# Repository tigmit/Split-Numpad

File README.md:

# DIY NUMPAD -
#####    by TIGMIT

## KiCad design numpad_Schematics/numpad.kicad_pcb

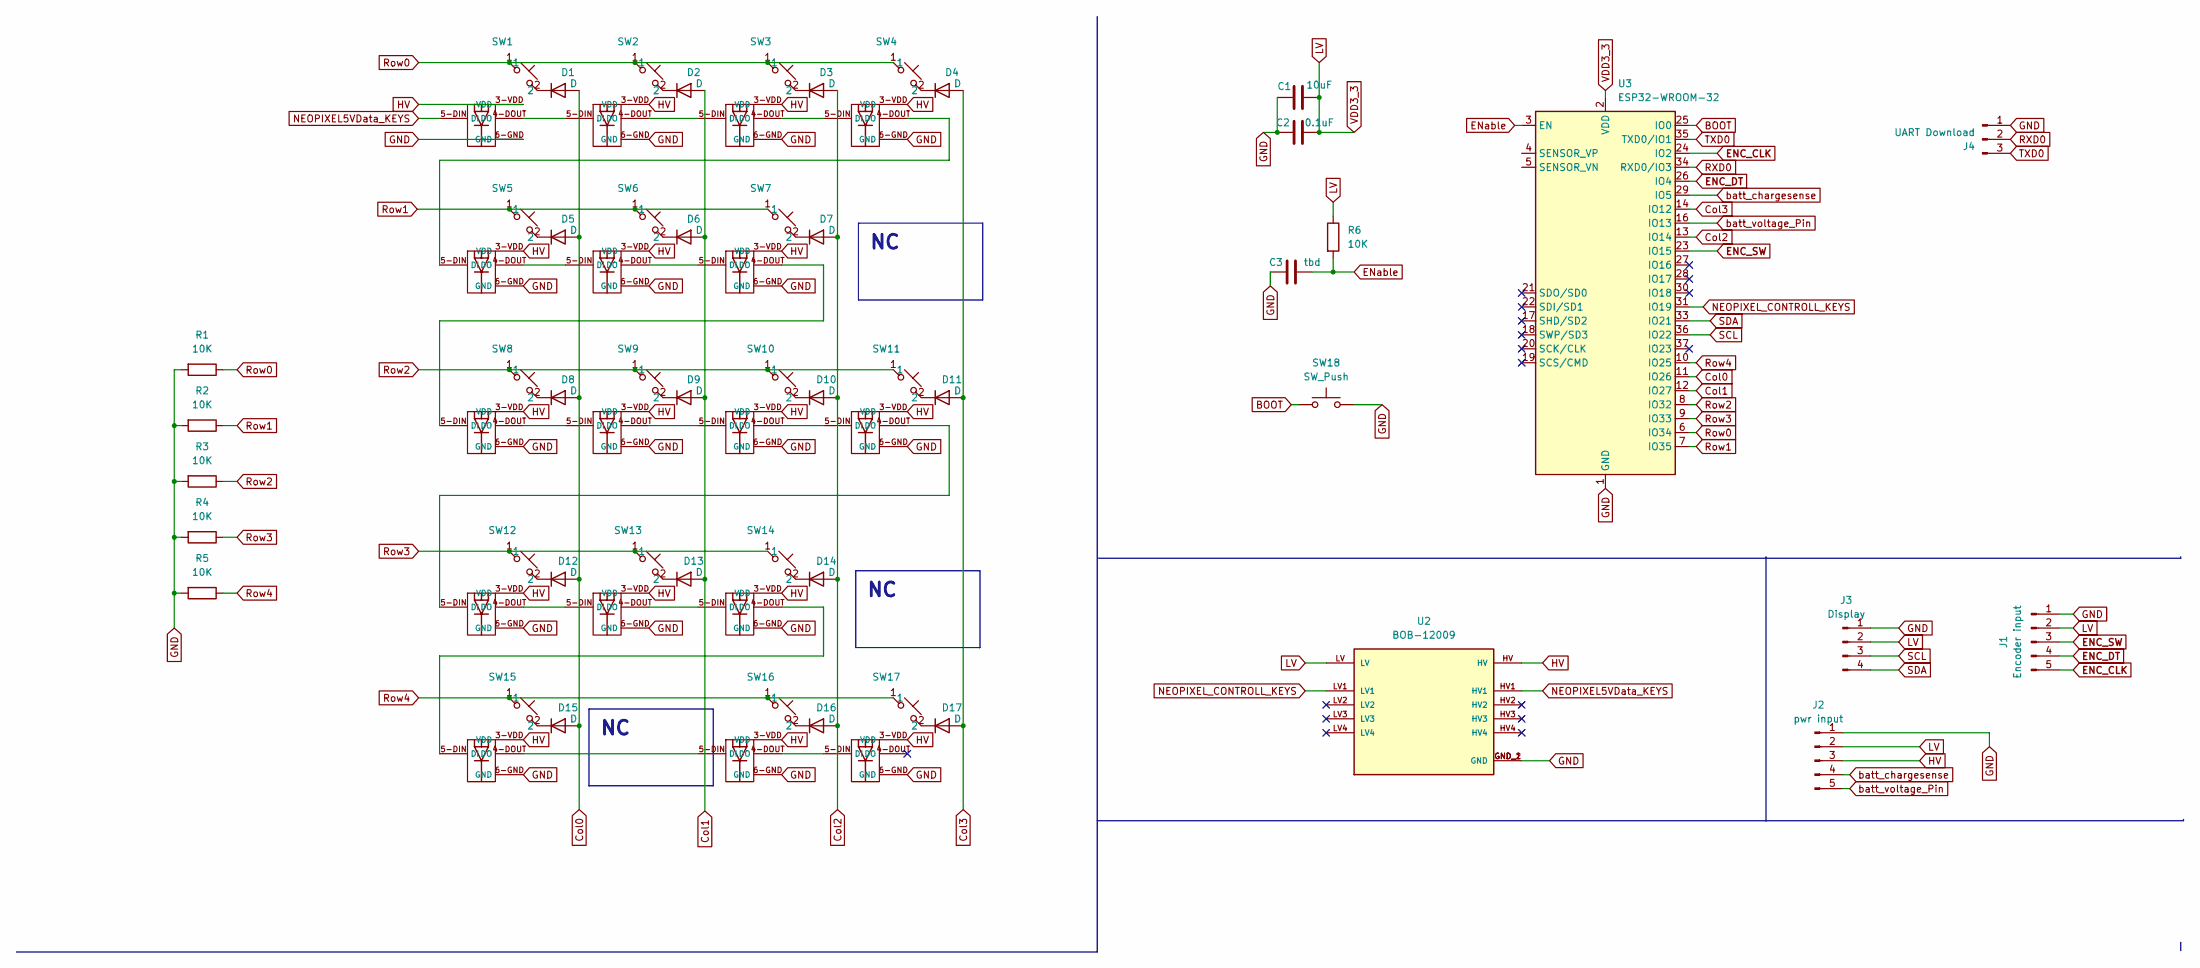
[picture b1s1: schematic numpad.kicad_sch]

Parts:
C1: 10uF; CP_EIA-3528-12_Kemet-T
C2: 0.1uF; CP_EIA-3528-12_Kemet-T
C3: tbd; CP_EIA-3528-12_Kemet-T
D1, D2, D3, D4, D5, D6, D7, D8, D9, D10, D11, D12, D13, D14, D15, D16, D17: D; Diode_SOD-123
J1: Encoder input; PinHeader_1x05_P2.54mm_Vertical
J2: pwr input; PinHeader_1x05_P2.54mm_Vertical
J3: Display; PinHeader_1x04_P2.54mm_Vertical
J4: UART Download; PinHeader_1x03_P2.54mm_Horizontal
R1, R2, R3, R4, R5, R6: 10K; R_Axial_DIN0204_L3.6mm_D1.6mm_P7.62mm_Horizontal
SW1, SW2, SW3, SW4, SW5, SW6, SW7, SW8, SW9, SW10, SW11, SW12, SW13, SW14, SW15, SW16, SW17: hotswap socket with neopixel
SW18: SW_Push; tigmit pushbutton
U2: BOB-12009; CONV_BOB-12009; PARTREV 01
U3: ESP32-WROOM-32; ESP32-WROOM-32 tigmit

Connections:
BOOT: SW18.1, U3.25 (IO0)
Col0: D1.2 (A), D5.2 (A), D8.2 (A), D12.2 (A), D15.2 (A), U3.11 (IO26)
Col1: D2.2 (A), D6.2 (A), D9.2 (A), D13.2 (A), U3.12 (IO27)
Col2: D3.2 (A), D7.2 (A), D10.2 (A), D14.2 (A), D16.2 (A), U3.13 (IO14)
Col3: D4.2 (A), D11.2 (A), D17.2 (A), U3.14 (IO12)
ENC_CLK: J1.5, U3.24 (IO2); also elsewhere on the board
ENC_DT: J1.4, U3.26 (IO4); also elsewhere on the board
ENC_SW: J1.3, U3.23 (IO15); also elsewhere on the board
ENable: C3.2, R6.2, U3.3 (EN)
GND: C1.1, C2.1, C3.1, J1.1, J2.1, J3.1, J4.1, R1.2, R2.2, R3.2, R4.2, R5.2, SW1.6-GND (GND), SW2.6-GND (GND), SW3.6-GND (GND), SW4.6-GND (GND), SW5.6-GND (GND), SW6.6-GND (GND), SW7.6-GND (GND), SW8.6-GND (GND), SW9.6-GND (GND), SW10.6-GND (GND), SW11.6-GND (GND), SW12.6-GND (GND), SW13.6-GND (GND), SW14.6-GND (GND), SW15.6-GND (GND), SW16.6-GND (GND), SW17.6-GND (GND), SW18.2, U2.GND_1 (GND), U2.GND_2 (GND), U3.1 (GND), U3.15 (GND), U3.38 (GND), U3.39 (GND); also elsewhere on the board
HV: J2.3, SW1.3-VDD (VDD), SW2.3-VDD (VDD), SW3.3-VDD (VDD), SW4.3-VDD (VDD), SW5.3-VDD (VDD), SW6.3-VDD (VDD), SW7.3-VDD (VDD), SW8.3-VDD (VDD), SW9.3-VDD (VDD), SW10.3-VDD (VDD), SW11.3-VDD (VDD), SW12.3-VDD (VDD), SW13.3-VDD (VDD), SW14.3-VDD (VDD), SW15.3-VDD (VDD), SW16.3-VDD (VDD), SW17.3-VDD (VDD), U2.HV; also elsewhere on the board
LV: C1.2, C2.2, J1.2, J2.2, J3.2, R6.1, U2.LV, U3.2 (VDD); also elsewhere on the board
NEOPIXEL5VData_KEYS: SW1.5-DIN (DI), U2.HV1; also elsewhere on the board
NEOPIXEL_CONTROLL_KEYS: U2.LV1, U3.31 (IO19); also elsewhere on the board
unnamed: D1.1 (K), SW1.2
unnamed: D2.1 (K), SW2.2
unnamed: D3.1 (K), SW3.2
unnamed: D4.1 (K), SW4.2
unnamed: D5.1 (K), SW5.2
unnamed: D6.1 (K), SW6.2
unnamed: D7.1 (K), SW7.2
unnamed: D8.1 (K), SW8.2
unnamed: D9.1 (K), SW9.2
unnamed: D10.1 (K), SW10.2
unnamed: D11.1 (K), SW11.2
unnamed: D12.1 (K), SW12.2
unnamed: D13.1 (K), SW13.2
unnamed: D14.1 (K), SW14.2
unnamed: D15.1 (K), SW15.2
unnamed: D16.1 (K), SW16.2
unnamed: D17.1 (K), SW17.2
unnamed: SW1.4-DOUT (DO), SW2.5-DIN (DI)
unnamed: SW2.4-DOUT (DO), SW3.5-DIN (DI)
unnamed: SW3.4-DOUT (DO), SW4.5-DIN (DI)
unnamed: SW4.4-DOUT (DO), SW5.5-DIN (DI)
unnamed: SW5.4-DOUT (DO), SW6.5-DIN (DI)
unnamed: SW6.4-DOUT (DO), SW7.5-DIN (DI)
unnamed: SW7.4-DOUT (DO), SW8.5-DIN (DI)
unnamed: SW8.4-DOUT (DO), SW9.5-DIN (DI)
unnamed: SW9.4-DOUT (DO), SW10.5-DIN (DI)
unnamed: SW10.4-DOUT (DO), SW11.5-DIN (DI)
unnamed: SW11.4-DOUT (DO), SW12.5-DIN (DI)
unnamed: SW12.4-DOUT (DO), SW13.5-DIN (DI)
unnamed: SW13.4-DOUT (DO), SW14.5-DIN (DI)
unnamed: SW14.4-DOUT (DO), SW15.5-DIN (DI)
unnamed: SW15.4-DOUT (DO), SW16.5-DIN (DI)
unnamed: SW16.4-DOUT (DO), SW17.5-DIN (DI)
RXD0: J4.2, U3.34 (RXD0/IO3); also elsewhere on the board
Row0: R1.1, SW1.1, SW2.1, SW3.1, SW4.1, U3.6 (IO34)
Row1: R2.1, SW5.1, SW6.1, SW7.1, U3.7 (IO35)
Row2: R3.1, SW8.1, SW9.1, SW10.1, SW11.1, U3.8 (IO32)
Row3: R4.1, SW12.1, SW13.1, SW14.1, U3.9 (IO33)
Row4: R5.1, SW15.1, SW16.1, SW17.1, U3.10 (IO25)
SCL: J3.3, U3.36 (IO22); also elsewhere on the board
SDA: J3.4, U3.33 (IO21); also elsewhere on the board
TXD0: J4.3, U3.35 (TXD0/IO1); also elsewhere on the board
batt_chargesense: J2.4, U3.29 (IO5); also elsewhere on the board
batt_voltage_Pin: J2.5, U3.16 (IO13); also elsewhere on the board

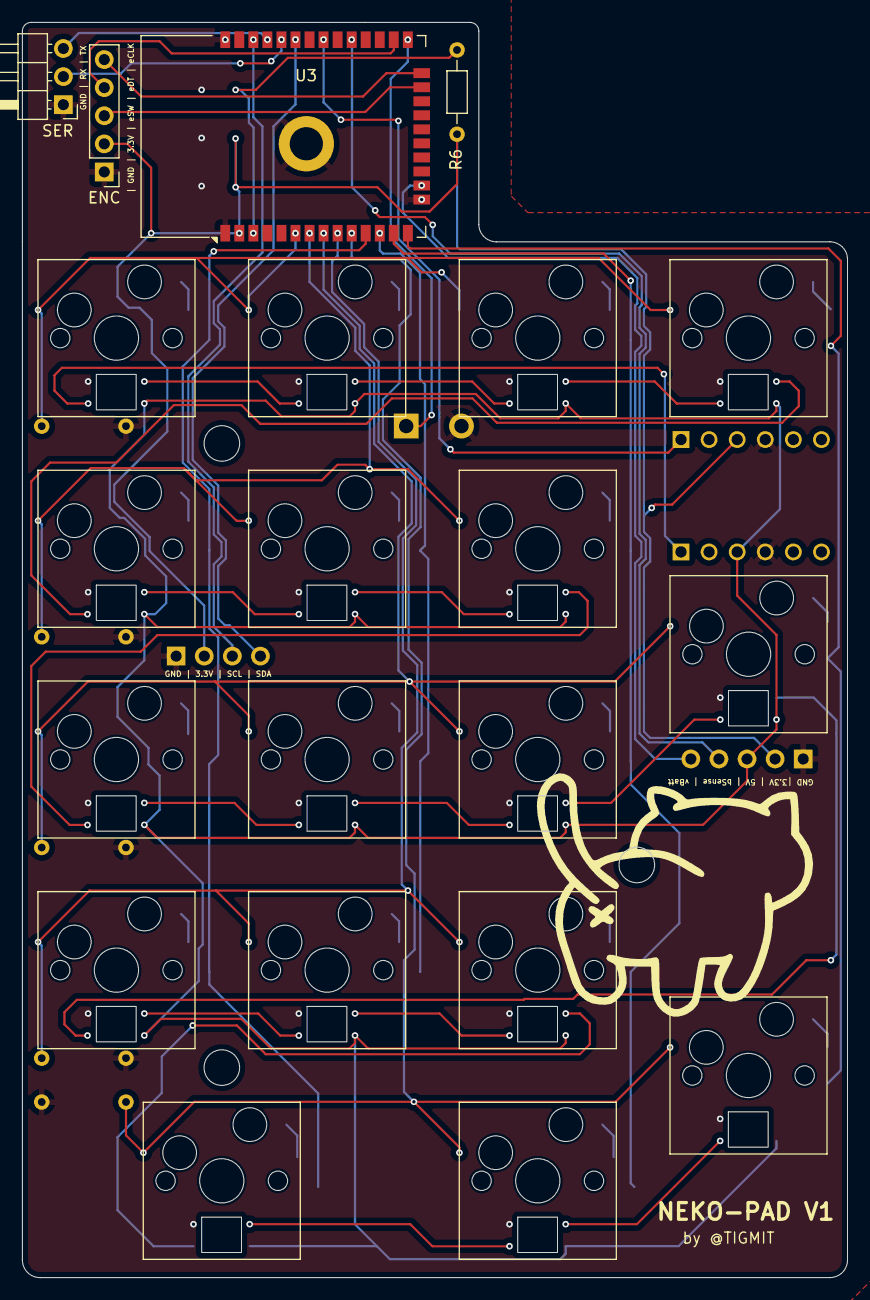
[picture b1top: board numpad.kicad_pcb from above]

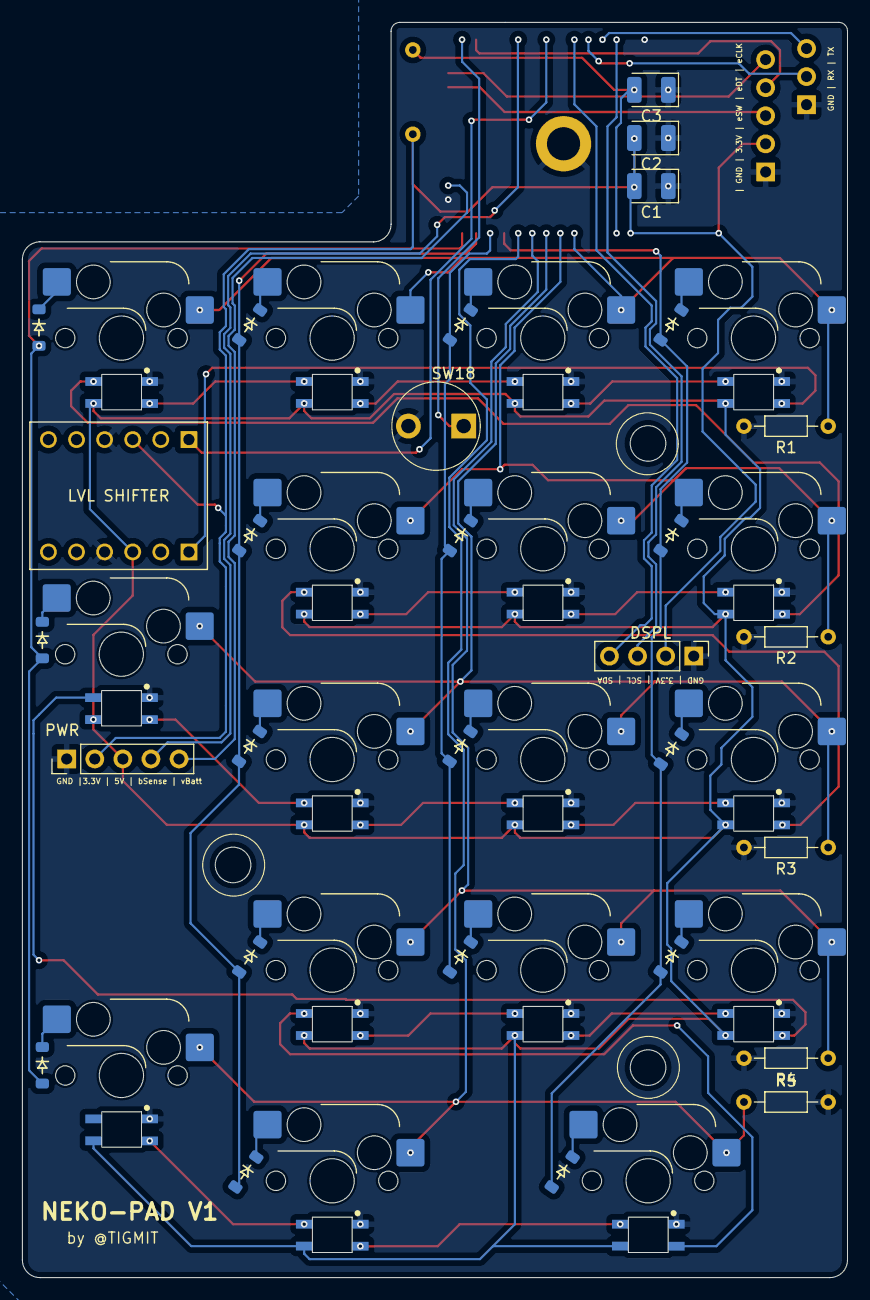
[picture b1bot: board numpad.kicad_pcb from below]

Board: 11 copper layers, 74.6 x 113.5 mm, 50 parts (29 on the bottom side), 58 nets.

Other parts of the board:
DSPL: Display; PinHeader_1x04_P2.54mm_Vertical
ENC: Encoder input; PinHeader_1x05_P2.54mm_Vertical
LVL SHIFTER: BOB-12009; CONV_BOB-12009
PWR: pwr input; PinHeader_1x05_P2.54mm_Vertical
SER: UART Download; PinHeader_1x03_P2.54mm_Horizontal

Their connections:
ENC_CLK: ENC.5; also elsewhere on the board
ENC_DT: ENC.4; also elsewhere on the board
ENC_SW: ENC.3; also elsewhere on the board
GND: DSPL.1, ENC.1, LVL SHIFTER.GND_1 (GND), LVL SHIFTER.GND_2 (GND), PWR.1, SER.1; also elsewhere on the board
HV: LVL SHIFTER.HV, PWR.3; also elsewhere on the board
LV: DSPL.2, ENC.2, LVL SHIFTER.LV, PWR.2; also elsewhere on the board
NEOPIXEL5VData_KEYS: LVL SHIFTER.HV1; also elsewhere on the board
NEOPIXEL_CONTROLL_KEYS: LVL SHIFTER.LV1; also elsewhere on the board
RXD0: SER.2; also elsewhere on the board
SCL: DSPL.3; also elsewhere on the board
SDA: DSPL.4; also elsewhere on the board
TXD0: SER.3; also elsewhere on the board
batt_chargesense: PWR.4; also elsewhere on the board
batt_voltage_Pin: PWR.5; also elsewhere on the board

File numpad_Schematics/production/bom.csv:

Designator,Footprint,Quantity,Value,LCSC Part #
C1,CP_EIA-3528-12_Kemet-T,1,10uF,
C2,CP_EIA-3528-12_Kemet-T,1,0.1uF,
C3,CP_EIA-3528-12_Kemet-T,1,tbd,
"D1, D10, D11, D12, D13, D14, D15, D16, D17, D2, D3, D4, D5, D6, D7, D8, D9",Diode_SOD-123,17,D,
DSPL,PinHeader_1x04_P2.54mm_Vertical,1,Display,
ENC,PinHeader_1x05_P2.54mm_Vertical,1,Encoder input,
LVL SHIFTER,CONV_BOB-12009,1,BOB-12009,
PWR,PinHeader_1x05_P2.54mm_Vertical,1,pwr input,
"R1, R2, R3, R4, R5, R6",R_Axial_DIN0204_L3.6mm_D1.6mm_P7.62mm_Horizontal,6,10K,
SER,PinHeader_1x03_P2.54mm_Horizontal,1,UART Download,
"SW1, SW10, SW11, SW12, SW13, SW14, SW15, SW16, SW17, SW2, SW3, SW4, SW5, SW6, SW7, SW8, SW9",hotswap socket with neopixel,17,~,
SW18,tigmit pushbutton,1,SW_Push,
U3,ESP32-WROOM-32 tigmit,1,ESP32-WROOM-32,

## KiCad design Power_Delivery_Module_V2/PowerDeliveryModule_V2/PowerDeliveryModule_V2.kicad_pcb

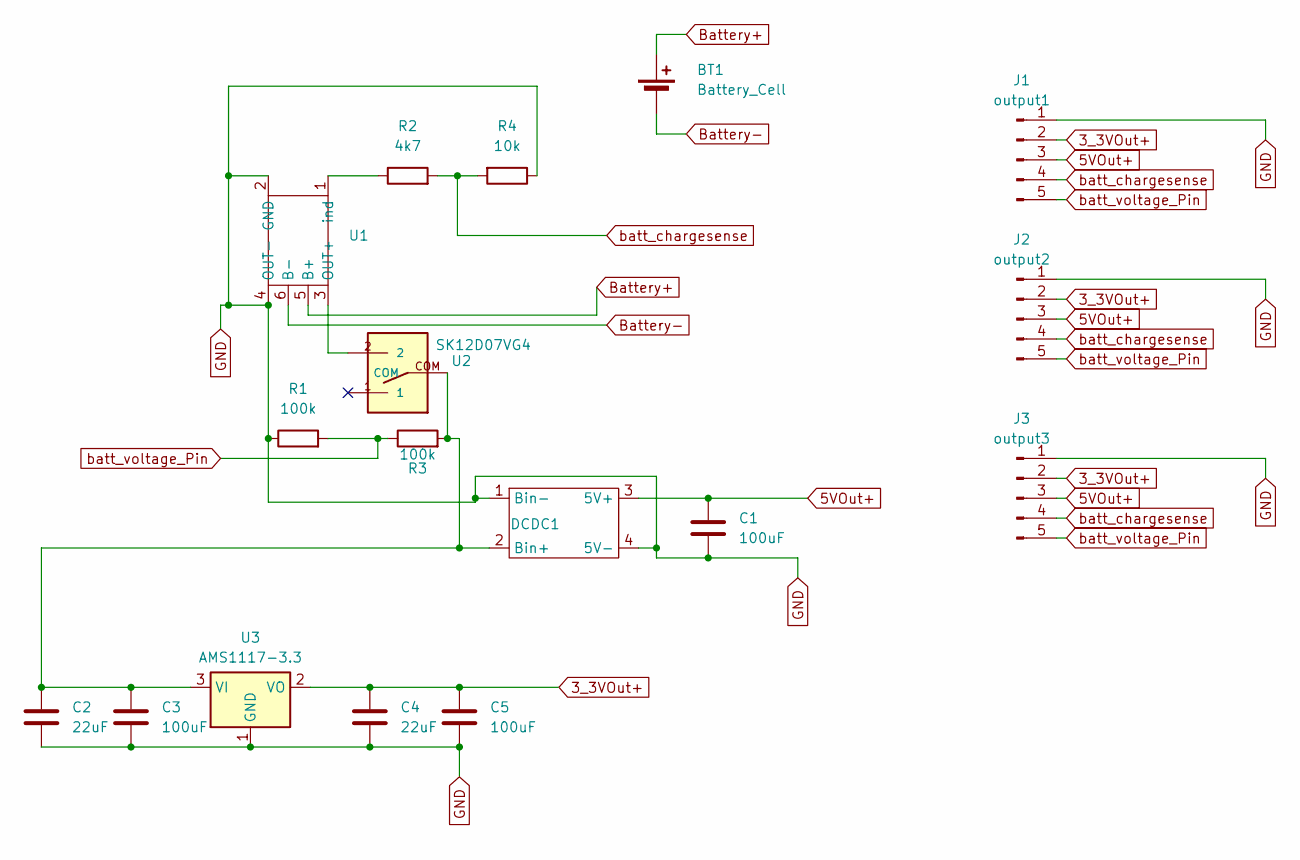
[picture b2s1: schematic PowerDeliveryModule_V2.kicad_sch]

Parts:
BT1: Battery_Cell; battery solder pins
C1, C3, C5: 100uF; CP_EIA-3528-12_Kemet-T
C2, C4: 22uF; CP_EIA-3528-12_Kemet-T
DCDC1: DCDC-Converter
J1: output1; PinHeader_1x05_P2.54mm_Vertical
J2: output2; PinHeader_1x05_P2.54mm_Vertical
J3: output3; PinHeader_1x05_P2.54mm_Vertical
R1, R3: 100k; R_Axial_DIN0204_L3.6mm_D1.6mm_P7.62mm_Horizontal
R2: 4k7; R_Axial_DIN0204_L3.6mm_D1.6mm_P7.62mm_Horizontal
R4: 10k; R_Axial_DIN0204_L3.6mm_D1.6mm_P7.62mm_Horizontal
U1: TP4056-18650
U2: SK12D07VG4
U3: AMS1117-3.3; SOT-223-3_TabPin2

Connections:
3_3VOut+: C4.1, C5.1, J1.2, J2.2, J3.2, U3.2 (VO)
5VOut+: C1.1, DCDC1.3 (5V+), J1.3, J2.3, J3.3
Battery+: BT1.1 (+), U1.5 (B+)
Battery-: BT1.2 (-), U1.6 (B-)
GND: C1.2, C2.2, C3.2, C4.2, C5.2, DCDC1.1 (Bin-), DCDC1.4 (5V-), J1.1, J2.1, J3.1, R1.1, R4.1, U1.2 (GND), U1.4 (OUT-), U3.1 (GND)
unnamed: C2.1, C3.1, DCDC1.2 (Bin+), R3.2, U2.COM, U3.3 (VI)
unnamed: U1.3 (OUT+), U2.2
unnamed: R2.1, U1.1 (ind)
batt_chargesense: J1.4, J2.4, J3.4, R2.2, R4.2
batt_voltage_Pin: J1.5, J2.5, J3.5, R1.2, R3.1

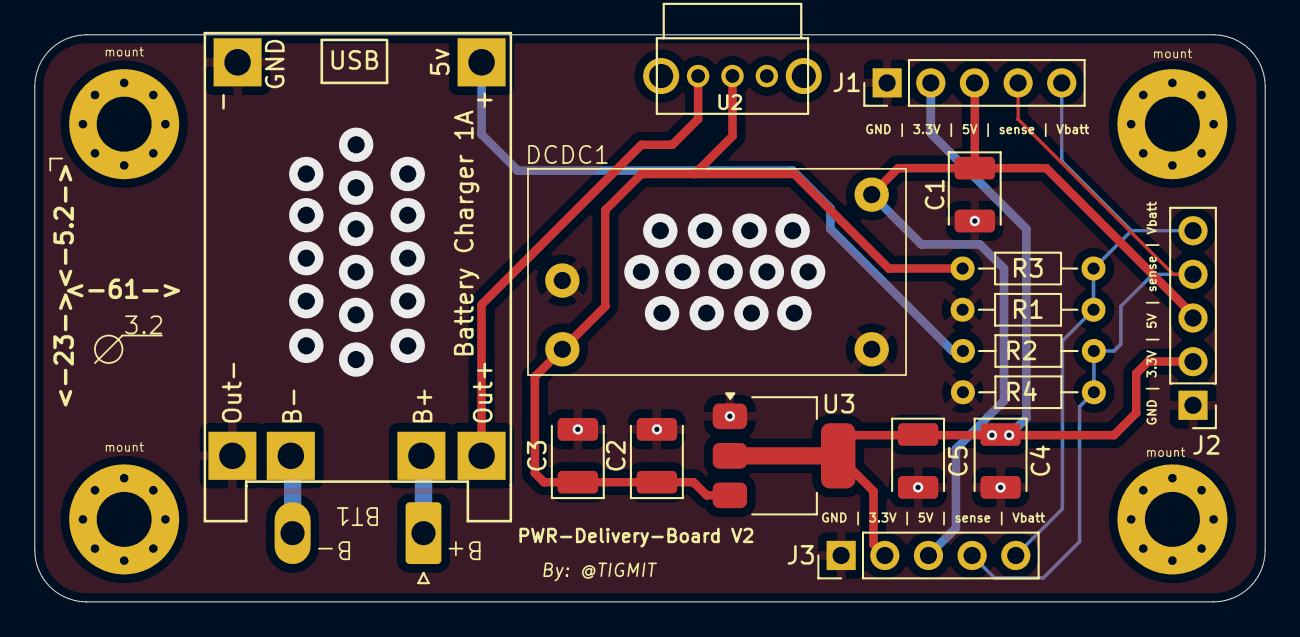
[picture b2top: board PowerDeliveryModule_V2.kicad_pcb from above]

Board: 2 copper layers, 71.6 x 33.0 mm, 21 parts (0 on the bottom side), 10 nets.

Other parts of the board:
mount: MountingHole_3.2mm_M3_Pad_Via
mount#2, mount#3, mount#4: MountingHole_3.2mm_M3_Pad_Via

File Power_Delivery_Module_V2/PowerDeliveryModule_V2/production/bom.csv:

Designator,Footprint,Quantity,Value,LCSC Part #
BT1,battery solder pins,1,Battery_Cell,
"C1, C3, C5",CP_EIA-3528-12_Kemet-T,3,100uF,
"C2, C4",CP_EIA-3528-12_Kemet-T,2,22uF,
DCDC1,DCDC-Converter,1,~,
J1,PinHeader_1x05_P2.54mm_Vertical,1,output1,
J2,PinHeader_1x05_P2.54mm_Vertical,1,output2,
J3,PinHeader_1x05_P2.54mm_Vertical,1,output3,
"R1, R3",R_Axial_DIN0204_L3.6mm_D1.6mm_P7.62mm_Horizontal,2,100k,
R2,R_Axial_DIN0204_L3.6mm_D1.6mm_P7.62mm_Horizontal,1,4k7,
R4,R_Axial_DIN0204_L3.6mm_D1.6mm_P7.62mm_Horizontal,1,10k,
U1,TP4056-18650,1,~,
U2,SK12D07VG4,1,SK12D07VG4,
U3,SOT-223-3_TabPin2,1,AMS1117-3.3,

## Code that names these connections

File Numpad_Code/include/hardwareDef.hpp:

/**
 * hardwareDef.hpp
 * brief   : defining the pins for the key matrix
 * created : 21.07.2024
 * creator : @tigmit
 * Licence : opensource
 */
#pragma once
#include <Arduino.h>

// baudrate Speed
static constexpr unsigned long serialBaudRate = 115200;

// Defines for keymatrix:
static constexpr uint8_t row0{34}; // input only pins
static constexpr uint8_t row1{35}; // input only pins
static constexpr uint8_t row2{32};
static constexpr uint8_t row3{33};
static constexpr uint8_t row4{25};

static constexpr uint8_t coll0{26};
static constexpr uint8_t coll1{27};
static constexpr uint8_t coll2{14};
static constexpr uint8_t coll3{12};

// Matrix dimentions
static constexpr uint8_t numRows{5};
static constexpr uint8_t numCols{4};
static constexpr uint8_t numLayers{1};

// Define on and off values
static constexpr bool OFF{0};
static constexpr bool ON{1};

// Display Defines
static constexpr uint8_t SCREEN_WIDTH{128}; // OLED display width, in pixels
static constexpr uint8_t SCREEN_HEIGHT{64}; // OLED display height, in pixels
static constexpr int8_t OLED_RESET{-1};     // Reset pin (-1 if default reset)
static constexpr uint8_t SCREEN_ADDRESS{0x3C}; // datasheet for refference

// pins for rotary Encoder
static constexpr int encCLK{2};  // CLK ENCODER
static constexpr int encDT{4};   // DT ENCODER
static constexpr int encBTN{15}; // encoder button

// LED defines
static constexpr uint8_t numLeds{17};
static constexpr uint8_t LedControllPin{19};

// battery is charging indicator
static constexpr uint8_t batteryChargeSense{5};

// reading the battery voltage through 33k / 100k voltage divider
static constexpr uint8_t batteryVoltage{13};

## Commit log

2024-07-21 working keyboard matrix and design files
2024-07-21 initialize all outputs to default LOW
2024-08-24 saving basic PCB design
2024-09-06 case and pcb design
2024-09-06 basic diasplay function and statemachine
2024-10-02 case design and some software changes
2024-10-12 base functionality including LED DSPL and KEYMATRIX
2024-10-13 push single RGB to Row-Col with color value
2024-10-14 fix Rtos panic
2024-10-15 implement Battery handling
2024-10-18 implement functionality and placeholder bitmap
2024-10-26 ble icon finalized + statechange to placeholder LED controll state
